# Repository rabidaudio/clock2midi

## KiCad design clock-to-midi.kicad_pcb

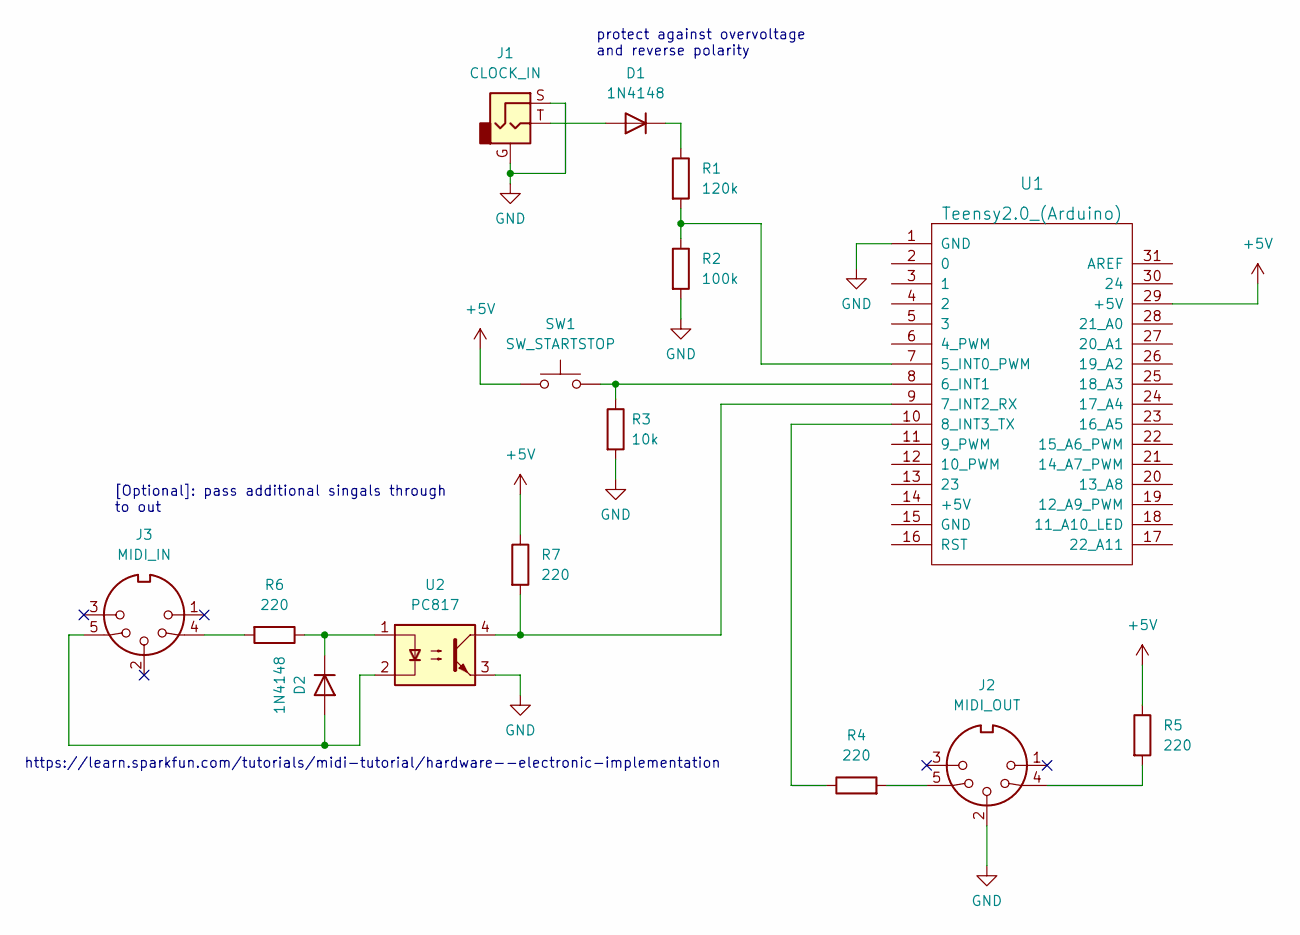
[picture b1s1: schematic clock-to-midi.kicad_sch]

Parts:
D1, D2: 1N4148; D_A-405_P2.54mm_Vertical_AnodeUp
J1: CLOCK_IN; PJ301M-12
J2: MIDI_OUT; DIN_5
J3: MIDI_IN; DIN_5
R1: 120k; R_Axial_DIN0204_L3.6mm_D1.6mm_P2.54mm_Vertical
R2: 100k; R_Axial_DIN0204_L3.6mm_D1.6mm_P2.54mm_Vertical
R3: 10k; R_Axial_DIN0204_L3.6mm_D1.6mm_P2.54mm_Vertical
R4, R5, R6, R7: 220; R_Axial_DIN0204_L3.6mm_D1.6mm_P2.54mm_Vertical
SW1: SW_STARTSTOP; SW_PUSH_6mm
U1: Teensy2.0_(Arduino); Teensy2.0
U2: PC817; DIP-4_W7.62mm

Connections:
+5V: R5.1, R7.1, SW1.1, U1.29 (+5V)
GND: J1.G, J1.S, J2.2, R2.2, R3.2, U1.1 (GND), U2.3
unnamed: D1.1 (K), R1.1
unnamed: D1.2 (A), J1.T
unnamed: D2.1 (K), R6.1, U2.1
unnamed: D2.2 (A), J3.5, U2.2
unnamed: J2.4, R5.2
unnamed: J2.5, R4.2
unnamed: J3.4, R6.2
unnamed: R1.2, R2.1, U1.7 (5_INT0_PWM)
unnamed: R3.1, SW1.2, U1.8 (6_INT1)
unnamed: R4.1, U1.10 (8_INT3_TX)
unnamed: R7.2, U1.9 (7_INT2_RX), U2.4

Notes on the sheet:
[Optional]: pass additional singals through to out
https://learn.sparkfun.com/tutorials/midi-tutorial/hardware--electronic-implementation
protect against overvoltage and reverse polarity

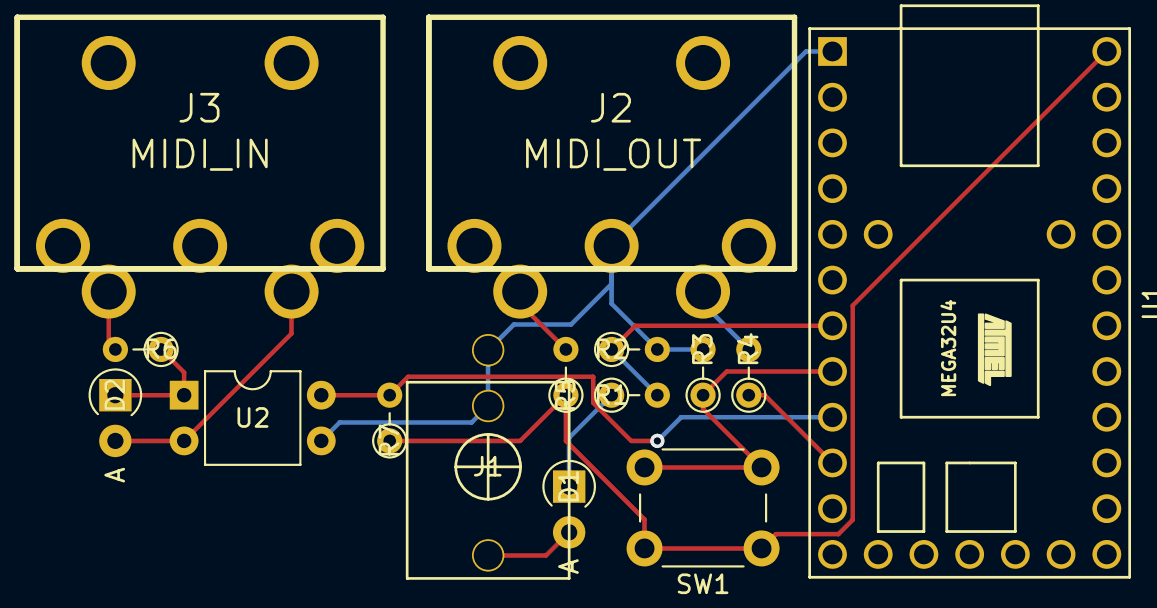
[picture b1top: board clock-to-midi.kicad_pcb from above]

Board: 2 copper layers, 15 parts (0 on the bottom side), 13 nets.

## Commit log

2023-05-30 working
2023-05-30 working timers
2023-05-30 refactor
2023-05-30 proof-of-concept
2023-05-30 made protoboard
